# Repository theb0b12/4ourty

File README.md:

# 40% keyb

A keyb project that I completed in about 3 hours.

Made with ergogen.

zmk repo is https://github.com/theb0b12/zmk-config-fourty

INFO:
- 45 keys
- 12.75u 40% keyb
  
TODO:
- [ ] update the case with
    - [ ] pcb angle, low profile mount mcu
- [ ] build said case

## below is wrong
The layout

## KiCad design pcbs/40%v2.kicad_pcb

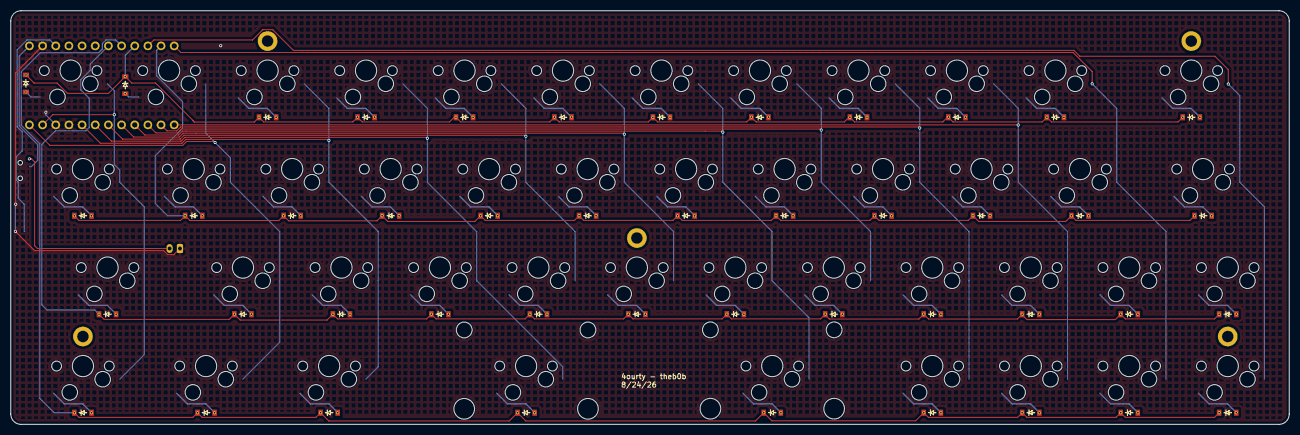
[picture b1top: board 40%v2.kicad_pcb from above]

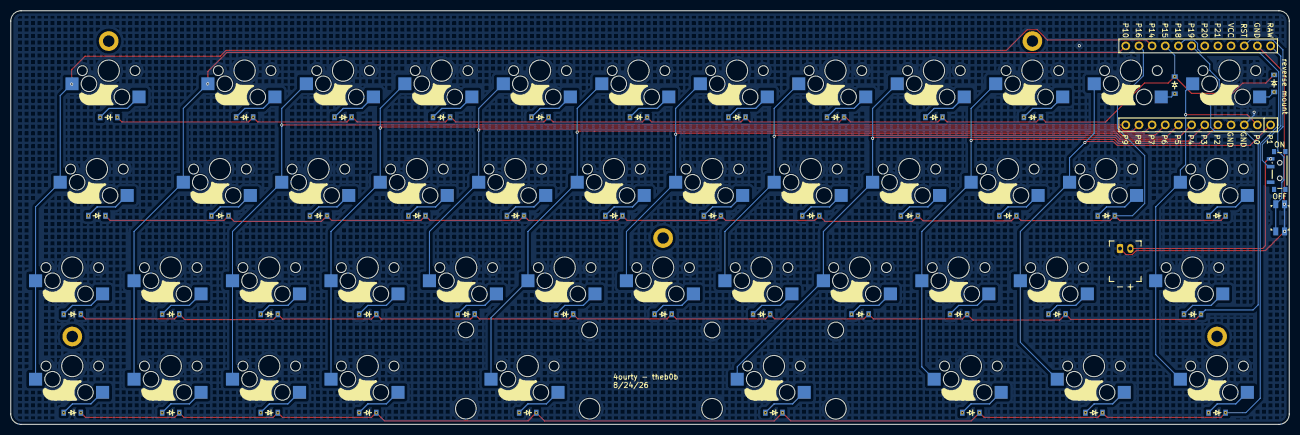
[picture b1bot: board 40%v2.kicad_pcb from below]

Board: 2 copper layers, 246.7 x 79.8 mm, 100 parts (49 on the bottom side), 65 nets.

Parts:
D1, D2, D3, D4, D5, D6, D7, D8, D9, D10, D11, D12, D13, D14, D15, D16, D17, D18, D19, D20, D21, D22, D23, D24, D25, D26, D27, D28, D29, D30, D31, D32, D33, D34, D35, D36, D37, D38, D39, D40, D41, D42, D43, D44, D45: ComboDiode
H1, H2, H3, H4, H5: mounting_hole_plated
JST1: battery_connector_jst_ph_2
MCU1: mcu_nice_nano
PWR1: power_switch_smd_side
REF: Stabilizer_MX_2.00u
RST1: reset_switch_smd_side
S1, S2, S3, S4, S5, S6, S7, S8, S9, S10, S11, S12, S13, S14, S15, S16, S17, S18, S19, S20, S21, S22, S23, S24, S25, S26, S27, S28, S29, S30, S31, S32, S33, S34, S35, S36, S37, S38, S39, S40, S41, S42, S43, S44, S45: switch_mx

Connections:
2nd_default: D38.1, D38.2, S38.2
BAT_P: JST1.2, PWR1.3
GND: JST1.1, MCU1.2, MCU1.21, MCU1.22, RST1.1, RST1.3
P0: MCU1.23, S1.1, S13.1, S25.1, S37.1
P1: MCU1.24, S2.1, S14.1, S26.1, S38.1
P2: MCU1.20, S3.1, S15.1, S27.1, S39.1
P3: MCU1.19, S4.1, S16.1, S28.1, S40.1
P4: MCU1.18, S5.1, S17.1, S29.1
P5: MCU1.17, S6.1, S18.1, S30.1
P6: MCU1.16, S7.1, S19.1, S31.1, S41.1
P7: MCU1.15, S8.1, S20.1, S32.1
P8: MCU1.14, S9.1, S21.1, S33.1, S42.1
P9: MCU1.13, S10.1, S22.1, S34.1, S43.1
P10: MCU1.12, S11.1, S23.1, S35.1, S44.1
P14: MCU1.10, S12.1, S24.1, S36.1, S45.1
P15: D1.1, D2.1, D3.1, D4.1, D5.1, D6.1, D7.1, D8.1, D9.1, D10.1, D11.1, D12.1, MCU1.9
P16: D13.1, D14.1, D15.1, D16.1, D17.1, D18.1, D19.1, D20.1, D21.1, D22.1, D23.1, D24.1, MCU1.11
P18: D37.1, D38.1, D39.1, D40.1, D41.1, D42.1, D43.1, D44.1, D45.1, MCU1.8
P19: D25.1, D26.1, D27.1, D28.1, D29.1, D30.1, D31.1, D32.1, D33.1, D34.1, D35.1, D36.1, MCU1.7
RAW: MCU1.1, PWR1.2
RST: MCU1.3, RST1.2, RST1.4
a_default: D14.1, D14.2, S14.2
alt_default: D39.1, D39.2, S39.2
arrow1_default: D43.1, D43.2, S43.2
arrow2_default: D44.1, D44.2, S44.2
arrow3_default: D45.1, D45.2, S45.2
b_default: D30.1, D30.2, S30.2
backspace_default: D12.1, D12.2, S12.2
c_default: D28.1, D28.2, S28.2
comma_default: D33.1, D33.2, S33.2
ctrl_default: D37.1, D37.2, S37.2
d_default: D16.1, D16.2, S16.2
e_default: D4.1, D4.2, S4.2
esc_default: D1.1, D1.2, S1.2
f_default: D17.1, D17.2, S17.2
fn_default: D42.1, D42.2, S42.2
g_default: D18.1, D18.2, S18.2
h_default: D19.1, D19.2, S19.2
i_default: D9.1, D9.2, S9.2
j_default: D20.1, D20.2, S20.2
k_default: D21.1, D21.2, S21.2
l_default: D22.1, D22.2, S22.2
m_default: D32.1, D32.2, S32.2
n_default: D31.1, D31.2, S31.2
o_default: D10.1, D10.2, S10.2
p_default: D11.1, D11.2, S11.2
period_default: D34.1, D34.2, S34.2
q_default: D2.1, D2.2, S2.2
questionmark_default: D35.1, D35.2, S35.2
quotes_default: D24.1, D24.2, S24.2
r_default: D5.1, D5.2, S5.2
s_default: D15.1, D15.2, S15.2
semicolon_default: D23.1, D23.2, S23.2
shift_default: D25.1, D25.2, S25.2
something_default: D36.1, D36.2, S36.2
space1_default: D40.1, D40.2, S40.2
space2_default: D41.1, D41.2, S41.2
t_default: D6.1, D6.2, S6.2
tab_default: D13.1, D13.2, S13.2
u_default: D8.1, D8.2, S8.2
v_default: D29.1, D29.2, S29.2
w_default: D3.1, D3.2, S3.2
x_default: D27.1, D27.2, S27.2
y_default: D7.1, D7.2, S7.2
z_default: D26.1, D26.2, S26.2

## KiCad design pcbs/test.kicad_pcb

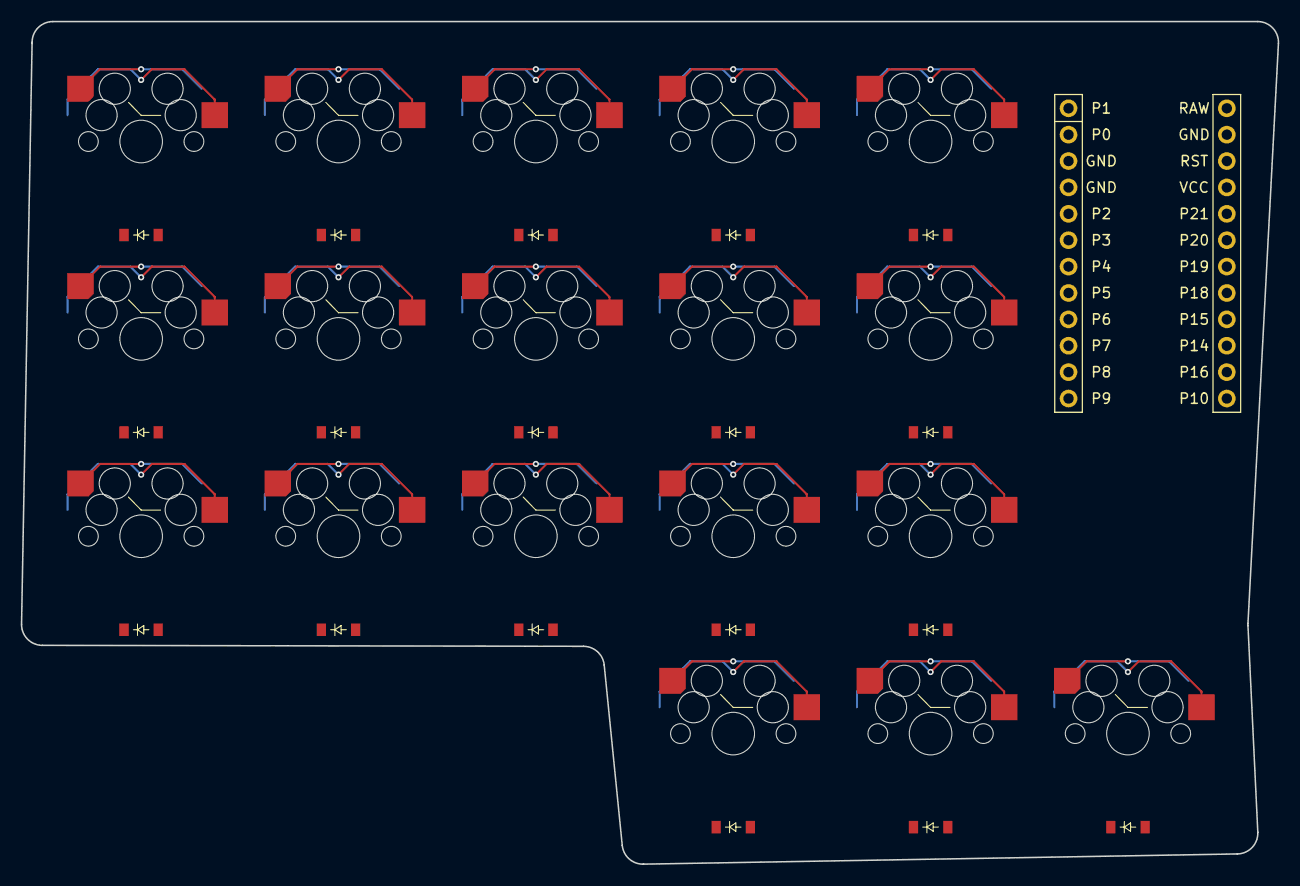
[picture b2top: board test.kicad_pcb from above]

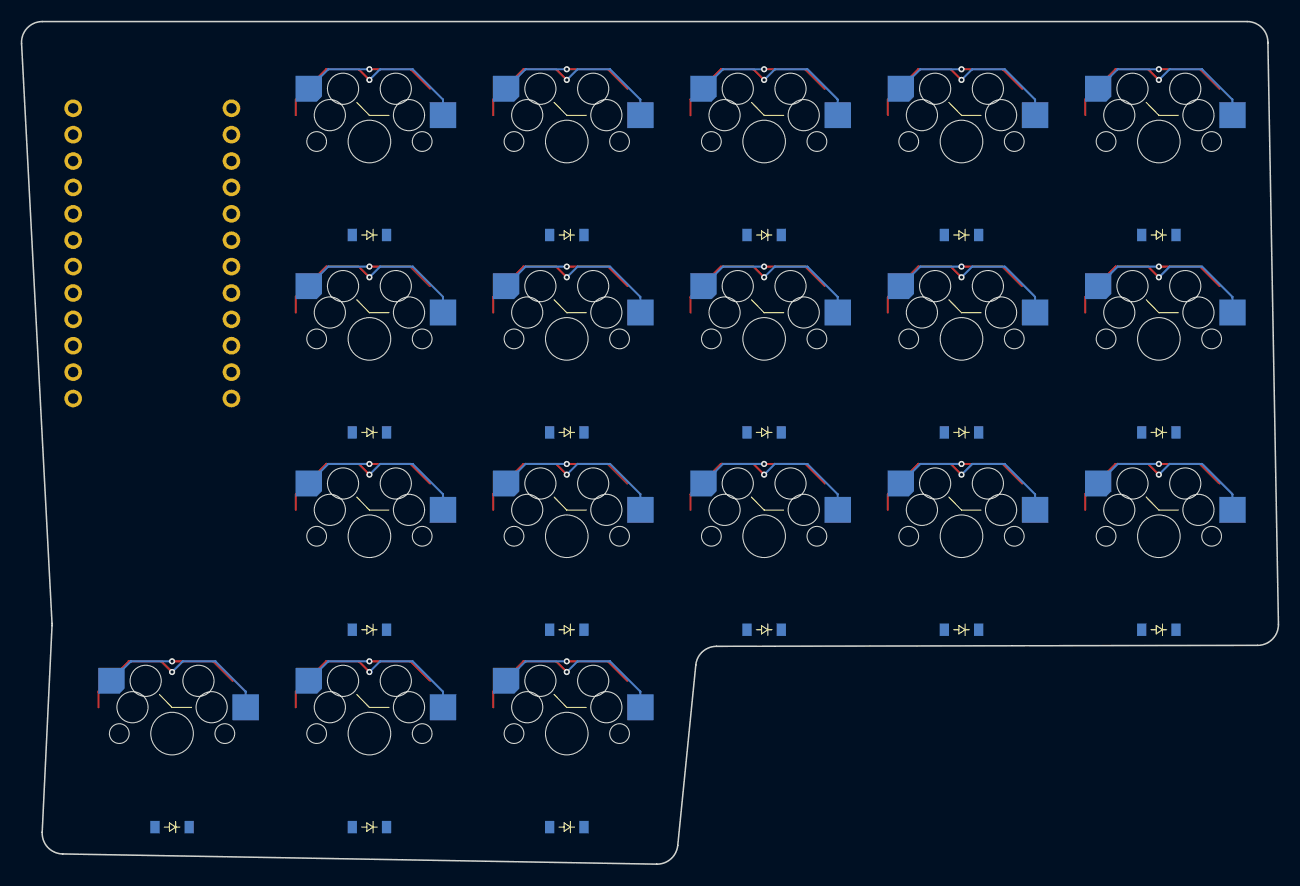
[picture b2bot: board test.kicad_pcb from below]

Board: 2 copper layers, 121.0 x 81.1 mm, 37 parts (18 on the bottom side), 19 nets.

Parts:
D1, D2, D3, D4, D5, D6, D7, D8, D9, D10, D11, D12, D13, D14, D15, D16, D17, D18: diode_tht_sod123
MCU1: mcu_nice_nano
S1, S2, S3, S4, S5, S6, S7, S8, S9, S10, S11, S12, S13, S14, S15, S16, S17, S18: switch_mx

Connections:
GND: MCU1.2, MCU1.21, MCU1.22
index_bottom: D10.2, S10.2
index_middle: D11.2, S11.2
index_top: D12.2, S12.2
inner_bottom: D13.2, S13.2
inner_middle: D14.2, S14.2
inner_top: D15.2, S15.2
middle_bottom: D7.2, S7.2
middle_middle: D8.2, S8.2
middle_thumb: D17.2, S17.2
middle_top: D9.2, S9.2
outer_thumb: D18.2, S18.2
pinky_bottom: D1.2, S1.2
pinky_middle: D2.2, S2.2
pinky_top: D3.2, S3.2
ring_bottom: D4.2, S4.2
ring_middle: D5.2, S5.2
ring_top: D6.2, S6.2
tuck_thumb: D16.2, S16.2
